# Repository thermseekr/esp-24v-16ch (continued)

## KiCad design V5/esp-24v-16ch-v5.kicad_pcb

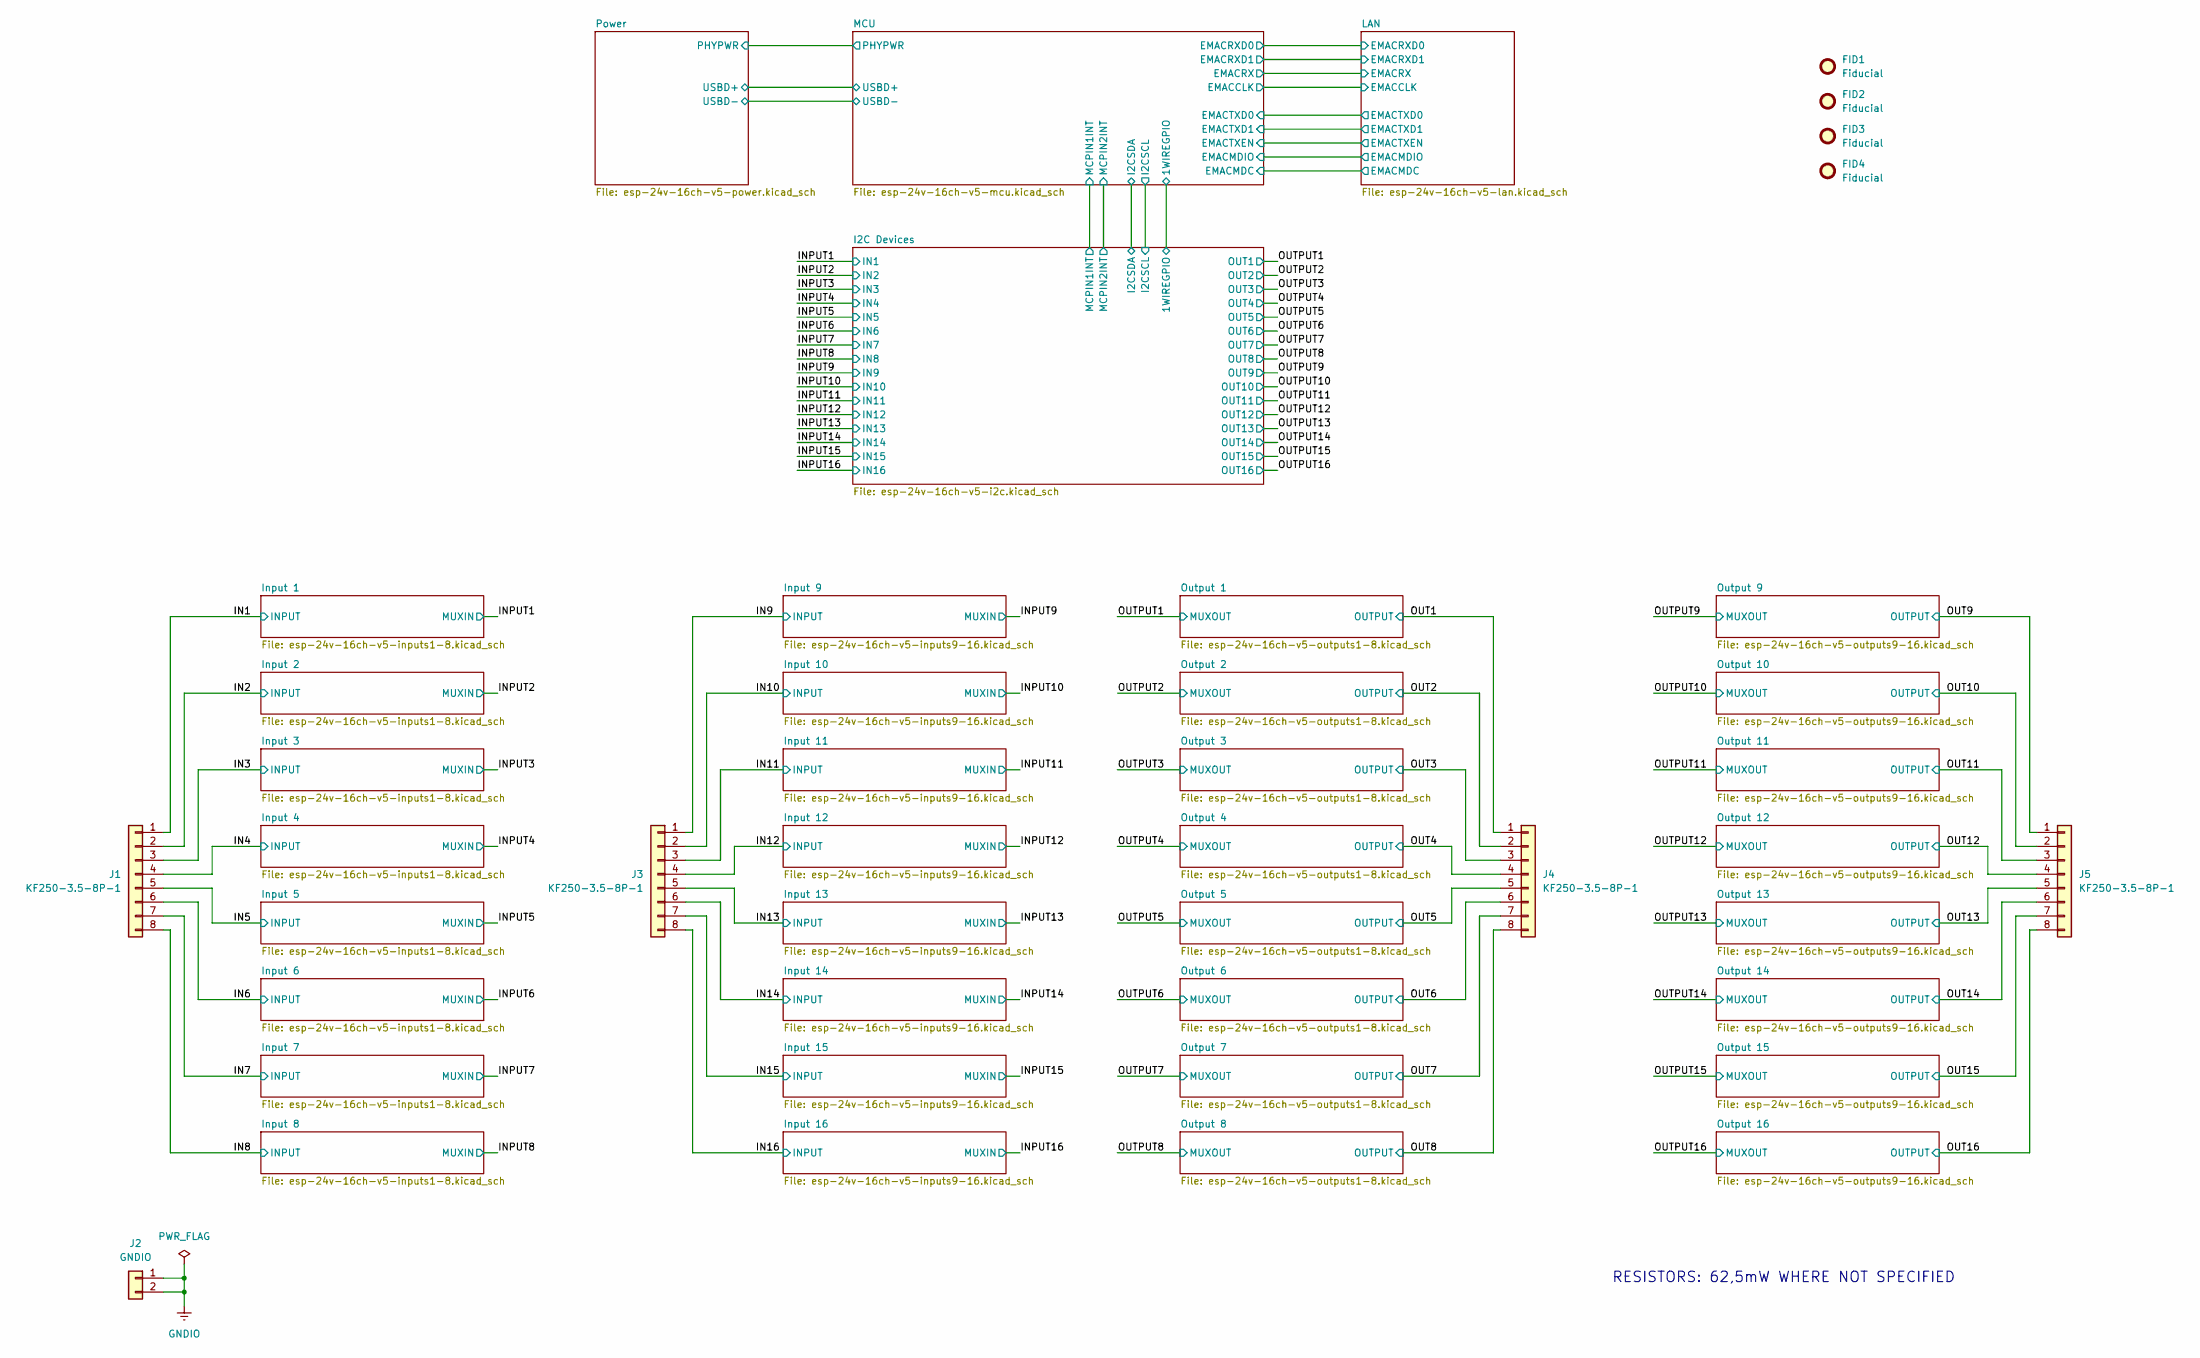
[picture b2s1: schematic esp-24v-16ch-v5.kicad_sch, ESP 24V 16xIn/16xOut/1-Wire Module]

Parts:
FID1, FID2, FID3, FID4: Fiducial; Fiducial_1mm_Mask2mm
J1, J3, J4, J5: KF250-3.5-8P-1; TerminalBlock_Wago_250-208_1x08_P3.5mm_45Degree; Mfr PN KF250-3.5-8P-1; JLCPCB BOM 1
J2: GNDIO; TerminalBlock_Wago_250-202_1x02_P3.5mm_45Degree; Mfr PN 250-202; JLCPCB BOM 1

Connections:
/IN1: J1.1; also elsewhere on the board
/IN2: J1.2; also elsewhere on the board
/IN3: J1.3; also elsewhere on the board
/IN4: J1.4; also elsewhere on the board
/IN5: J1.5; also elsewhere on the board
/IN6: J1.6; also elsewhere on the board
/IN7: J1.7; also elsewhere on the board
/IN8: J1.8; also elsewhere on the board
/IN9: J3.1; also elsewhere on the board
/IN10: J3.2; also elsewhere on the board
/IN11: J3.3; also elsewhere on the board
/IN12: J3.4; also elsewhere on the board
/IN13: J3.5; also elsewhere on the board
/IN14: J3.6; also elsewhere on the board
/IN15: J3.7; also elsewhere on the board
/IN16: J3.8; also elsewhere on the board
/OUT1: J4.1; also elsewhere on the board
/OUT2: J4.2; also elsewhere on the board
/OUT3: J4.3; also elsewhere on the board
/OUT4: J4.4; also elsewhere on the board
/OUT5: J4.5; also elsewhere on the board
/OUT6: J4.6; also elsewhere on the board
/OUT7: J4.7; also elsewhere on the board
/OUT8: J4.8; also elsewhere on the board
/OUT9: J5.1; also elsewhere on the board
/OUT10: J5.2; also elsewhere on the board
/OUT11: J5.3; also elsewhere on the board
/OUT12: J5.4; also elsewhere on the board
/OUT13: J5.5; also elsewhere on the board
/OUT14: J5.6; also elsewhere on the board
/OUT15: J5.7; also elsewhere on the board
/OUT16: J5.8; also elsewhere on the board
GNDIO: J2.1, J2.2; also elsewhere on the board

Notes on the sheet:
RESISTORS: 62,5mW WHERE NOT SPECIFIED

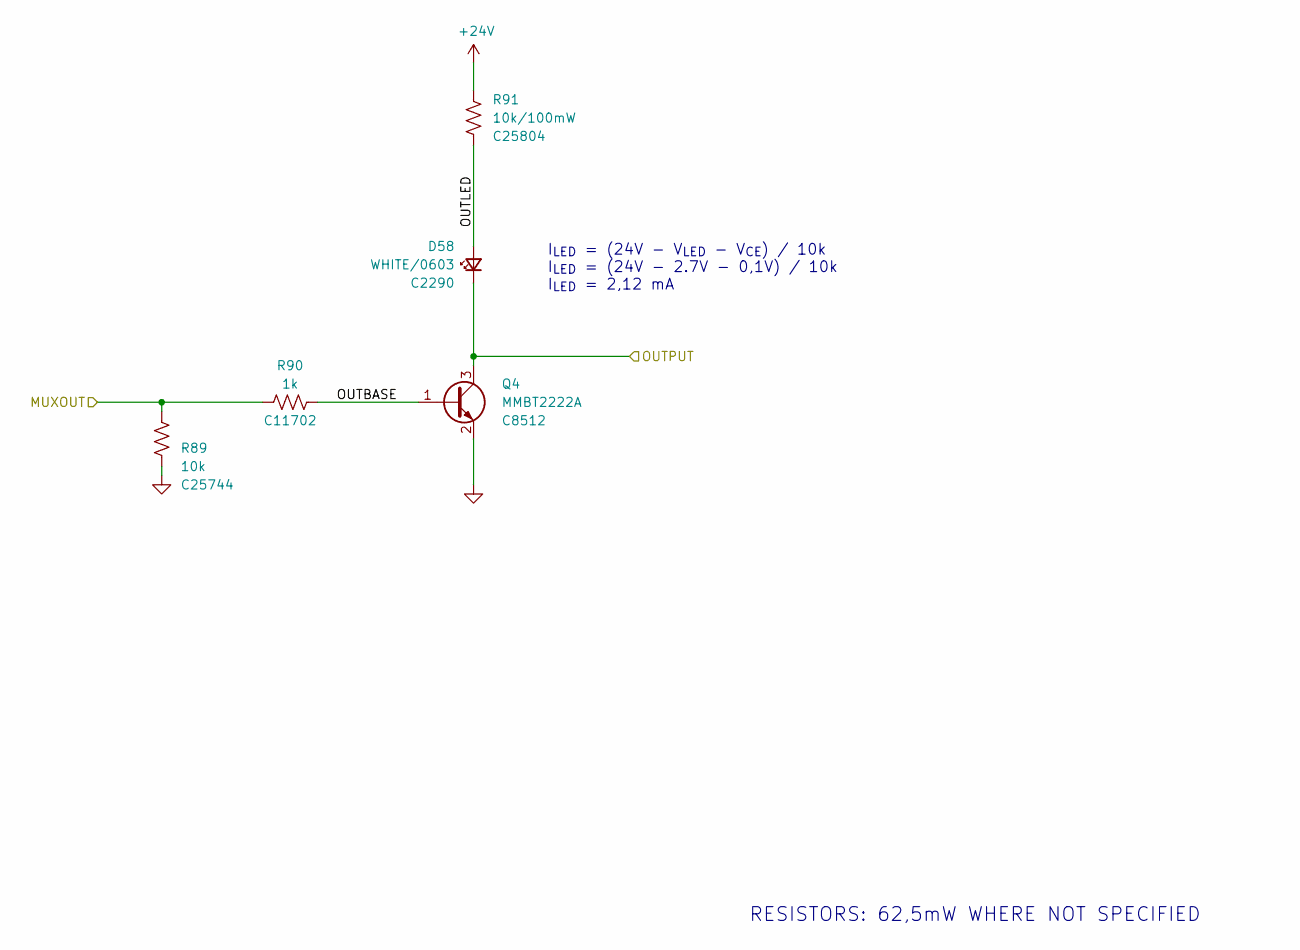
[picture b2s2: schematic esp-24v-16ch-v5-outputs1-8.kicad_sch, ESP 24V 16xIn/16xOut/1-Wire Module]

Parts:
D58: WHITE/0603; LED_0603_1608Metric; Mfr PN KT-0603W; LCSC Part # C2290
Q4: MMBT2222A; SOT-23-Narrow; Mfr PN MMBT2222A; JLCPCB BOM 1
R89: 10k; R_0402_1005Metric; Mfr PN 0402WGF1002TCE; LCSC Part # C25744
R90: 1k; R_0402_1005Metric; Mfr PN 0402WGF1001TCE; LCSC Part # C11702
R91: 10k/100mW; R_0603_1608Metric; Mfr PN 0603WAF1002T5E; LCSC Part # C25804

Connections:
+24V: R91.1; also elsewhere on the board
/OUT1: D58.1 (K), Q4.3 (C); also elsewhere on the board
/OUTPUT1: R89.2, R90.2; also elsewhere on the board
/Output 1/OUTBASE: Q4.1 (B), R90.1
/Output 1/OUTLED: D58.2 (A), R91.2
GND: Q4.2 (E), R89.1; also elsewhere on the board

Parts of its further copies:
D59, D60, D61, D62, D63, D64, D65: WHITE/0603; LED_0603_1608Metric; Mfr PN KT-0603W; LCSC Part # C2290
Q5, Q6, Q7, Q8, Q9, Q10, Q11: MMBT2222A; SOT-23-Narrow; Mfr PN MMBT2222A; JLCPCB BOM 1
R92, R95, R98, R101, R104, R107, R110: 10k; R_0402_1005Metric; Mfr PN 0402WGF1002TCE; LCSC Part # C25744
R93, R96, R99, R102, R105, R108, R111: 1k; R_0402_1005Metric; Mfr PN 0402WGF1001TCE; LCSC Part # C11702
R94, R97, R100, R103, R106, R109, R112: 10k/100mW; R_0603_1608Metric; Mfr PN 0603WAF1002T5E; LCSC Part # C25804

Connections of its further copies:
+24V: R94.1, R97.1, R100.1, R103.1, R106.1, R109.1, R112.1; also elsewhere on the board
/OUT2: D59.1 (K), Q5.3 (C); also elsewhere on the board
/OUT3: D60.1 (K), Q6.3 (C); also elsewhere on the board
/OUT4: D61.1 (K), Q7.3 (C); also elsewhere on the board
/OUT5: D62.1 (K), Q8.3 (C); also elsewhere on the board
/OUT6: D63.1 (K), Q9.3 (C); also elsewhere on the board
/OUT7: D64.1 (K), Q10.3 (C); also elsewhere on the board
/OUT8: D65.1 (K), Q11.3 (C); also elsewhere on the board
/OUTPUT2: R92.2, R93.2; also elsewhere on the board
/OUTPUT3: R95.2, R96.2; also elsewhere on the board
/OUTPUT4: R98.2, R99.2; also elsewhere on the board
/OUTPUT5: R101.2, R102.2; also elsewhere on the board
/OUTPUT6: R104.2, R105.2; also elsewhere on the board
/OUTPUT7: R107.2, R108.2; also elsewhere on the board
/OUTPUT8: R110.2, R111.2; also elsewhere on the board
/Output 2/OUTBASE: Q5.1 (B), R93.1
/Output 2/OUTLED: D59.2 (A), R94.2
/Output 3/OUTBASE: Q6.1 (B), R96.1
/Output 3/OUTLED: D60.2 (A), R97.2
/Output 4/OUTBASE: Q7.1 (B), R99.1
/Output 4/OUTLED: D61.2 (A), R100.2
/Output 5/OUTBASE: Q8.1 (B), R102.1
/Output 5/OUTLED: D62.2 (A), R103.2
/Output 6/OUTBASE: Q9.1 (B), R105.1
/Output 6/OUTLED: D63.2 (A), R106.2
/Output 7/OUTBASE: Q10.1 (B), R108.1
/Output 7/OUTLED: D64.2 (A), R109.2
/Output 8/OUTBASE: Q11.1 (B), R111.1
/Output 8/OUTLED: D65.2 (A), R112.2
GND: Q5.2 (E), Q6.2 (E), Q7.2 (E), Q8.2 (E), Q9.2 (E), Q10.2 (E), Q11.2 (E), R92.1, R95.1, R98.1, R101.1, R104.1, R107.1, R110.1; also elsewhere on the board

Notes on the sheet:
I_{LED} = (24V - V_{LED} - V_{CE}) / 10k I_{LED} = (24V - 2.7V - 0,1V) / 10k I_{LED} = 2,12 mA
RESISTORS: 62,5mW WHERE NOT SPECIFIED

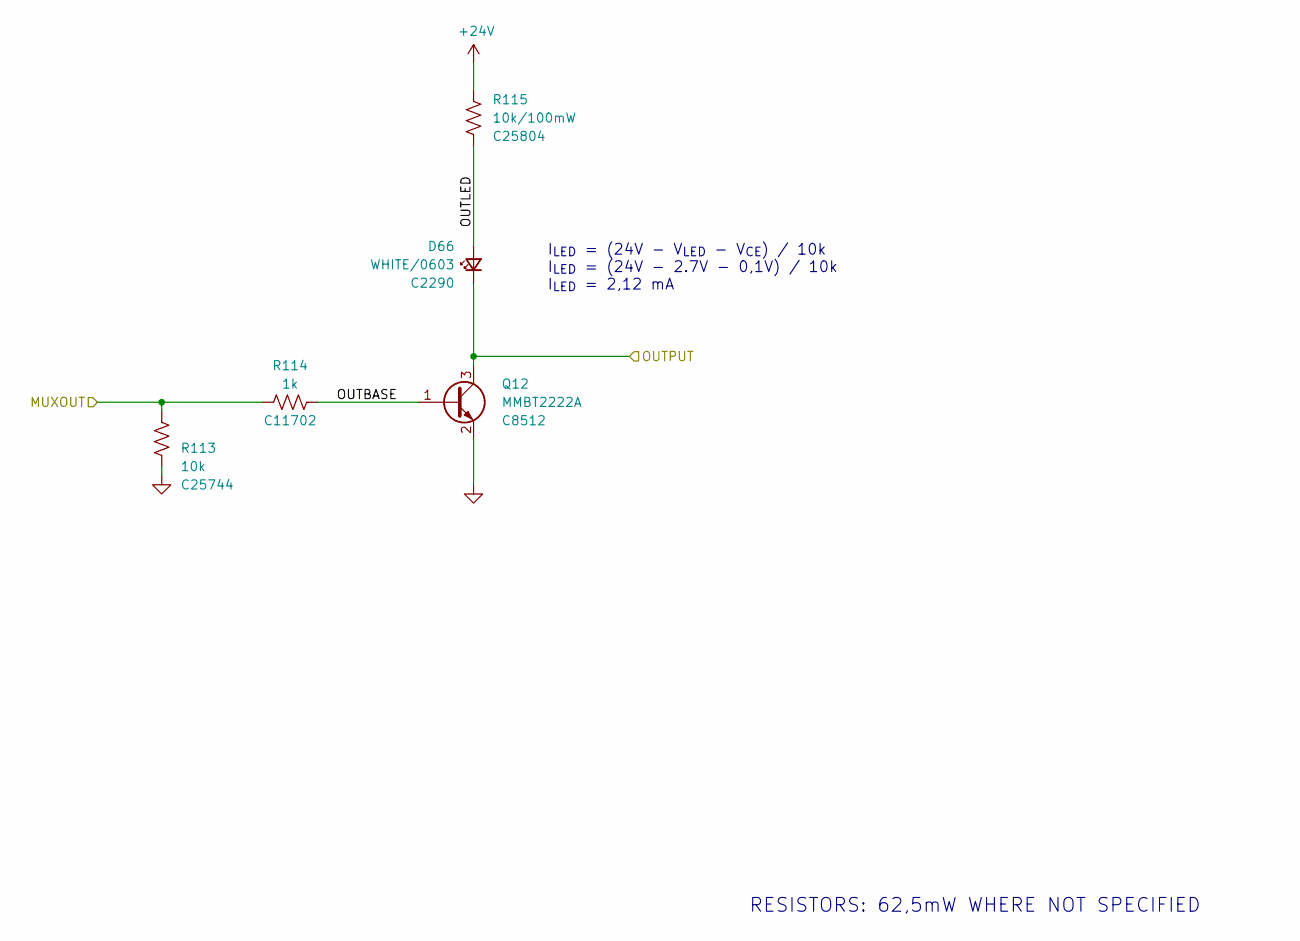
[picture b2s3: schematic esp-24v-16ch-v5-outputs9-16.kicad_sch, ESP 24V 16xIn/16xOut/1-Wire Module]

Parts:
D66: WHITE/0603; LED_0603_1608Metric; Mfr PN KT-0603W; LCSC Part # C2290
Q12: MMBT2222A; SOT-23-Narrow; Mfr PN MMBT2222A; JLCPCB BOM 1
R113: 10k; R_0402_1005Metric; Mfr PN 0402WGF1002TCE; LCSC Part # C25744
R114: 1k; R_0402_1005Metric; Mfr PN 0402WGF1001TCE; LCSC Part # C11702
R115: 10k/100mW; R_0603_1608Metric; Mfr PN 0603WAF1002T5E; LCSC Part # C25804

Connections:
+24V: R115.1; also elsewhere on the board
/OUT9: D66.1 (K), Q12.3 (C); also elsewhere on the board
/OUTPUT9: R113.2, R114.2; also elsewhere on the board
/Output 9/OUTBASE: Q12.1 (B), R114.1
/Output 9/OUTLED: D66.2 (A), R115.2
GND: Q12.2 (E), R113.1; also elsewhere on the board

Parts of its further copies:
D67, D68, D69, D70, D71, D72, D73: WHITE/0603; LED_0603_1608Metric; Mfr PN KT-0603W; LCSC Part # C2290
Q13, Q14, Q15, Q16, Q17, Q18, Q19: MMBT2222A; SOT-23-Narrow; Mfr PN MMBT2222A; JLCPCB BOM 1
R116, R119, R122, R125, R128, R131, R134: 10k; R_0402_1005Metric; Mfr PN 0402WGF1002TCE; LCSC Part # C25744
R117, R120, R123, R126, R129, R132, R135: 1k; R_0402_1005Metric; Mfr PN 0402WGF1001TCE; LCSC Part # C11702
R118, R121, R124, R127, R130, R133, R136: 10k/100mW; R_0603_1608Metric; Mfr PN 0603WAF1002T5E; LCSC Part # C25804

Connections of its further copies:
+24V: R118.1, R121.1, R124.1, R127.1, R130.1, R133.1, R136.1; also elsewhere on the board
/OUT10: D67.1 (K), Q13.3 (C); also elsewhere on the board
/OUT11: D68.1 (K), Q14.3 (C); also elsewhere on the board
/OUT12: D69.1 (K), Q15.3 (C); also elsewhere on the board
/OUT13: D70.1 (K), Q16.3 (C); also elsewhere on the board
/OUT14: D71.1 (K), Q17.3 (C); also elsewhere on the board
/OUT15: D72.1 (K), Q18.3 (C); also elsewhere on the board
/OUT16: D73.1 (K), Q19.3 (C); also elsewhere on the board
/OUTPUT10: R116.2, R117.2; also elsewhere on the board
/OUTPUT11: R119.2, R120.2; also elsewhere on the board
/OUTPUT12: R122.2, R123.2; also elsewhere on the board
/OUTPUT13: R125.2, R126.2; also elsewhere on the board
/OUTPUT14: R128.2, R129.2; also elsewhere on the board
/OUTPUT15: R131.2, R132.2; also elsewhere on the board
/OUTPUT16: R134.2, R135.2; also elsewhere on the board
/Output 10/OUTBASE: Q13.1 (B), R117.1
/Output 10/OUTLED: D67.2 (A), R118.2
/Output 11/OUTBASE: Q14.1 (B), R120.1
/Output 11/OUTLED: D68.2 (A), R121.2
/Output 12/OUTBASE: Q15.1 (B), R123.1
/Output 12/OUTLED: D69.2 (A), R124.2
/Output 13/OUTBASE: Q16.1 (B), R126.1
/Output 13/OUTLED: D70.2 (A), R127.2
/Output 14/OUTBASE: Q17.1 (B), R129.1
/Output 14/OUTLED: D71.2 (A), R130.2
/Output 15/OUTBASE: Q18.1 (B), R132.1
/Output 15/OUTLED: D72.2 (A), R133.2
/Output 16/OUTBASE: Q19.1 (B), R135.1
/Output 16/OUTLED: D73.2 (A), R136.2
GND: Q13.2 (E), Q14.2 (E), Q15.2 (E), Q16.2 (E), Q17.2 (E), Q18.2 (E), Q19.2 (E), R116.1, R119.1, R122.1, R125.1, R128.1, R131.1, R134.1; also elsewhere on the board

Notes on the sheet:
RESISTORS: 62,5mW WHERE NOT SPECIFIED
I_{LED} = (24V - V_{LED} - V_{CE}) / 10k I_{LED} = (24V - 2.7V - 0,1V) / 10k I_{LED} = 2,12 mA

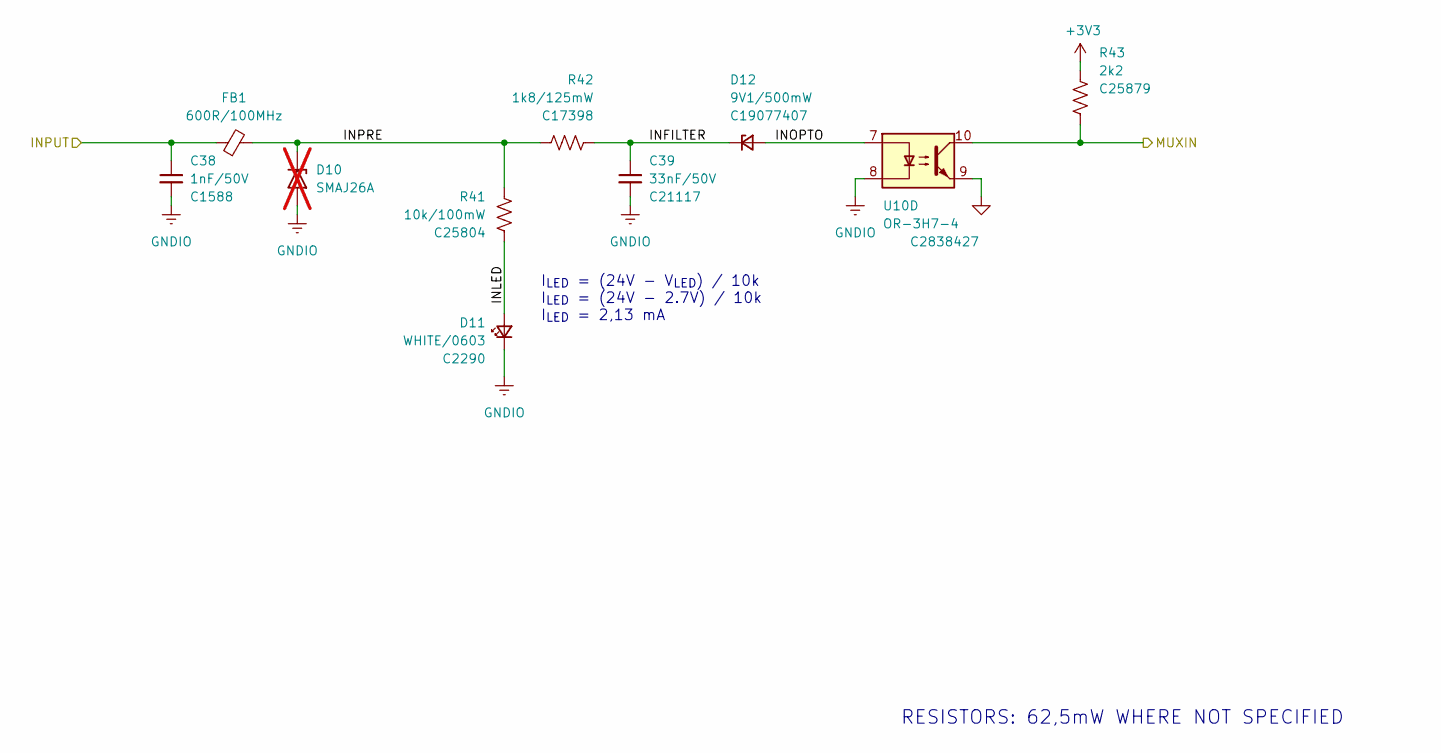
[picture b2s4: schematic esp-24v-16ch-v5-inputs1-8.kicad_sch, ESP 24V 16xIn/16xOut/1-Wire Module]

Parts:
C38: 1nF/50V; C_0603_1608Metric; Mfr PN CL10B102KB8NNNC; LCSC Part # C1588
C39: 33nF/50V; C_0603_1608Metric; Mfr PN CL10B333KB8NNNC; LCSC Part # C21117
D10: SMAJ26A; D_SMA; Mfr PN SMAJ26A; JLCPCB BOM 1; not fitted
D11: WHITE/0603; LED_0603_1608Metric; Mfr PN KT-0603W; LCSC Part # C2290
D12: 9V1/500mW; D_SOD-123; Mfr PN BZT52C9V1; JLCPCB BOM 1
FB1: 600R/100MHz; R_0603_1608Metric; Mfr PN BLM18KG601SN1D; JLCPCB BOM 1
R41: 10k/100mW; R_0603_1608Metric; Mfr PN 0603WAF1002T5E; LCSC Part # C25804
R42: 1k8/125mW; R_0805_2012Metric; Mfr PN 0805W8F1801T5E; LCSC Part # C17398
R43: 2k2; R_0402_1005Metric; Mfr PN 0402WGF2201TCE; LCSC Part # C25879
U10: OR-3H7-4; SOP-16_4.4x10.4mm_P1.27mm; Mfr PN OR-3H7-4GB-TA1-G; JLCPCB BOM 1

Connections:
+3V3: R43.1; also elsewhere on the board
/IN1: C38.1, FB1.1; also elsewhere on the board
/INPUT1: R43.2, U10.10; also elsewhere on the board
/INPUT2: U10.12; also elsewhere on the board
/INPUT3: U10.14; also elsewhere on the board
/INPUT4: U10.16; also elsewhere on the board
/Input 1/INFILTER: C39.1, D12.1 (K), R42.1
/Input 1/INLED: D11.2 (A), R41.2
/Input 1/INOPTO: D12.2 (A), U10.7
/Input 1/INPRE: FB1.2, R41.1, R42.2
/Input 2/INOPTO: U10.5; also elsewhere on the board
/Input 3/INOPTO: U10.3; also elsewhere on the board
/Input 4/INOPTO: U10.1; also elsewhere on the board
GND: U10.9, U10.11, U10.13, U10.15; also elsewhere on the board
GNDIO: C38.2, C39.2, D10.2 (A2), D11.1 (K), U10.2, U10.4, U10.6, U10.8; also elsewhere on the board

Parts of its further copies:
C40, C42, C44, C46, C48, C50, C52: 1nF/50V; C_0603_1608Metric; Mfr PN CL10B102KB8NNNC; LCSC Part # C1588
C41, C43, C45, C47, C49, C51, C53: 33nF/50V; C_0603_1608Metric; Mfr PN CL10B333KB8NNNC; LCSC Part # C21117
D14, D17, D20, D23, D26, D29, D32: WHITE/0603; LED_0603_1608Metric; Mfr PN KT-0603W; LCSC Part # C2290
D15, D18, D21, D24, D27, D30, D33: 9V1/500mW; D_SOD-123; Mfr PN BZT52C9V1; JLCPCB BOM 1
FB2, FB3, FB4, FB5, FB6, FB7, FB8: 600R/100MHz; R_0603_1608Metric; Mfr PN BLM18KG601SN1D; JLCPCB BOM 1
R44, R47, R50, R53, R56, R59, R62: 10k/100mW; R_0603_1608Metric; Mfr PN 0603WAF1002T5E; LCSC Part # C25804
R45, R48, R51, R54, R57, R60, R63: 1k8/125mW; R_0805_2012Metric; Mfr PN 0805W8F1801T5E; LCSC Part # C17398
R46, R49, R52, R55, R58, R61, R64: 2k2; R_0402_1005Metric; Mfr PN 0402WGF2201TCE; LCSC Part # C25879
U11: OR-3H7-4; SOP-16_4.4x10.4mm_P1.27mm; Mfr PN OR-3H7-4GB-TA1-G; JLCPCB BOM 1

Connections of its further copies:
+3V3: R46.1, R49.1, R52.1, R55.1, R58.1, R61.1, R64.1; also elsewhere on the board
/IN2: C40.1, FB2.1; also elsewhere on the board
/IN3: C42.1, FB3.1; also elsewhere on the board
/IN4: C44.1, FB4.1; also elsewhere on the board
/IN5: C46.1, FB5.1; also elsewhere on the board
/IN6: C48.1, FB6.1; also elsewhere on the board
/IN7: C50.1, FB7.1; also elsewhere on the board
/IN8: C52.1, FB8.1; also elsewhere on the board
/INPUT2: R46.2; also elsewhere on the board
/INPUT3: R49.2; also elsewhere on the board
/INPUT4: R52.2; also elsewhere on the board
/INPUT5: R55.2, U11.10; also elsewhere on the board
/INPUT6: R58.2, U11.12; also elsewhere on the board
/INPUT7: R61.2, U11.14; also elsewhere on the board
/INPUT8: R64.2, U11.16; also elsewhere on the board
/Input 2/INFILTER: C41.1, D15.1 (K), R45.1
/Input 2/INLED: D14.2 (A), R44.2
/Input 2/INOPTO: D15.2 (A); also elsewhere on the board
/Input 2/INPRE: FB2.2, R44.1, R45.2
/Input 3/INFILTER: C43.1, D18.1 (K), R48.1
/Input 3/INLED: D17.2 (A), R47.2
/Input 3/INOPTO: D18.2 (A); also elsewhere on the board
/Input 3/INPRE: FB3.2, R47.1, R48.2
/Input 4/INFILTER: C45.1, D21.1 (K), R51.1
/Input 4/INLED: D20.2 (A), R50.2
/Input 4/INOPTO: D21.2 (A); also elsewhere on the board
/Input 4/INPRE: FB4.2, R50.1, R51.2
/Input 5/INFILTER: C47.1, D24.1 (K), R54.1
/Input 5/INLED: D23.2 (A), R53.2
/Input 5/INOPTO: D24.2 (A), U11.7
/Input 5/INPRE: FB5.2, R53.1, R54.2
/Input 6/INFILTER: C49.1, D27.1 (K), R57.1
/Input 6/INLED: D26.2 (A), R56.2
/Input 6/INOPTO: D27.2 (A), U11.5
/Input 6/INPRE: FB6.2, R56.1, R57.2
/Input 7/INFILTER: C51.1, D30.1 (K), R60.1
/Input 7/INLED: D29.2 (A), R59.2
/Input 7/INOPTO: D30.2 (A), U11.3
/Input 7/INPRE: FB7.2, R59.1, R60.2
/Input 8/INFILTER: C53.1, D33.1 (K), R63.1
/Input 8/INLED: D32.2 (A), R62.2
/Input 8/INOPTO: D33.2 (A), U11.1
/Input 8/INPRE: FB8.2, R62.1, R63.2
GND: U11.9, U11.11, U11.13, U11.15; also elsewhere on the board
GNDIO: C40.2, C41.2, C42.2, C43.2, C44.2, C45.2, C46.2, C47.2, C48.2, C49.2, C50.2, C51.2, C52.2, C53.2, D14.1 (K), D17.1 (K), D20.1 (K), D23.1 (K), D26.1 (K), D29.1 (K), D32.1 (K), U11.2, U11.4, U11.6, U11.8; also elsewhere on the board

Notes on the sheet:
I_{LED} = (24V - V_{LED}) / 10k I_{LED} = (24V - 2.7V) / 10k I_{LED} = 2,13 mA
RESISTORS: 62,5mW WHERE NOT SPECIFIED

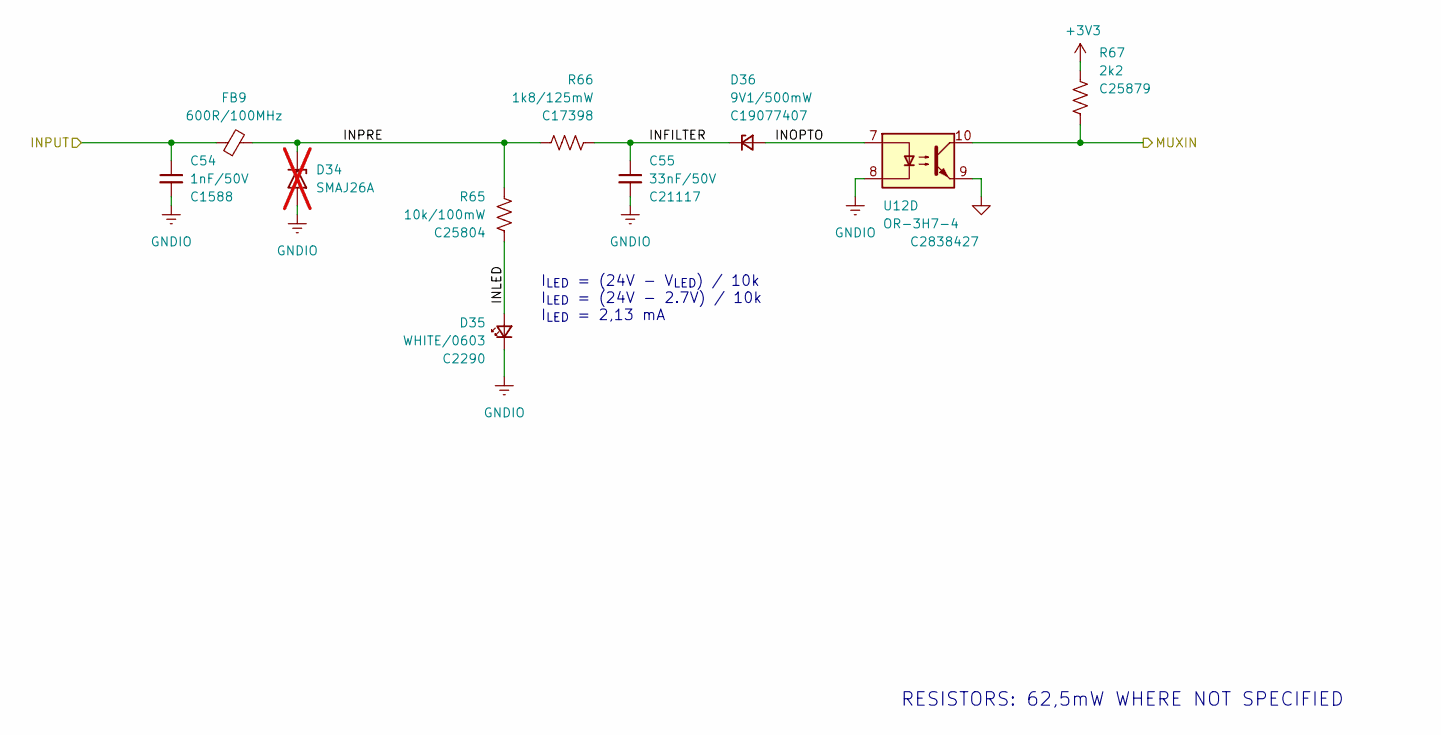
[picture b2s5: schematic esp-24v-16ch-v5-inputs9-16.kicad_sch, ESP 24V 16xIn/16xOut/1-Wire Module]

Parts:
C54: 1nF/50V; C_0603_1608Metric; Mfr PN CL10B102KB8NNNC; LCSC Part # C1588
C55: 33nF/50V; C_0603_1608Metric; Mfr PN CL10B333KB8NNNC; LCSC Part # C21117
D34: SMAJ26A; D_SMA; Mfr PN SMAJ26A; JLCPCB BOM 1; not fitted
D35: WHITE/0603; LED_0603_1608Metric; Mfr PN KT-0603W; LCSC Part # C2290
D36: 9V1/500mW; D_SOD-123; Mfr PN BZT52C9V1; JLCPCB BOM 1
FB9: 600R/100MHz; R_0603_1608Metric; Mfr PN BLM18KG601SN1D; JLCPCB BOM 1
R65: 10k/100mW; R_0603_1608Metric; Mfr PN 0603WAF1002T5E; LCSC Part # C25804
R66: 1k8/125mW; R_0805_2012Metric; Mfr PN 0805W8F1801T5E; LCSC Part # C17398
R67: 2k2; R_0402_1005Metric; Mfr PN 0402WGF2201TCE; LCSC Part # C25879
U12: OR-3H7-4; SOP-16_4.4x10.4mm_P1.27mm; Mfr PN OR-3H7-4GB-TA1-G; JLCPCB BOM 1

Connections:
+3V3: R67.1; also elsewhere on the board
/IN9: C54.1, FB9.1; also elsewhere on the board
/INPUT9: R67.2, U12.10; also elsewhere on the board
/INPUT10: U12.12; also elsewhere on the board
/INPUT11: U12.14; also elsewhere on the board
/INPUT12: U12.16; also elsewhere on the board
/Input 9/INFILTER: C55.1, D36.1 (K), R66.1
/Input 9/INLED: D35.2 (A), R65.2
/Input 9/INOPTO: D36.2 (A), U12.7
/Input 9/INPRE: FB9.2, R65.1, R66.2
/Input 10/INOPTO: U12.5; also elsewhere on the board
/Input 11/INOPTO: U12.3; also elsewhere on the board
/Input 12/INOPTO: U12.1; also elsewhere on the board
GND: U12.9, U12.11, U12.13, U12.15; also elsewhere on the board
GNDIO: C54.2, C55.2, D34.2 (A2), D35.1 (K), U12.2, U12.4, U12.6, U12.8; also elsewhere on the board

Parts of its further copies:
C56, C58, C60, C62, C64, C66, C68: 1nF/50V; C_0603_1608Metric; Mfr PN CL10B102KB8NNNC; LCSC Part # C1588
C57, C59, C61, C63, C65, C67, C69: 33nF/50V; C_0603_1608Metric; Mfr PN CL10B333KB8NNNC; LCSC Part # C21117
D38, D41, D44, D47, D50, D53, D56: WHITE/0603; LED_0603_1608Metric; Mfr PN KT-0603W; LCSC Part # C2290
D39, D42, D45, D48, D51, D54, D57: 9V1/500mW; D_SOD-123; Mfr PN BZT52C9V1; JLCPCB BOM 1
FB10, FB11, FB12, FB13, FB14, FB15, FB16: 600R/100MHz; R_0603_1608Metric; Mfr PN BLM18KG601SN1D; JLCPCB BOM 1
R68, R71, R74, R77, R80, R83, R86: 10k/100mW; R_0603_1608Metric; Mfr PN 0603WAF1002T5E; LCSC Part # C25804
R69, R72, R75, R78, R81, R84, R87: 1k8/125mW; R_0805_2012Metric; Mfr PN 0805W8F1801T5E; LCSC Part # C17398
R70, R73, R76, R79, R82, R85, R88: 2k2; R_0402_1005Metric; Mfr PN 0402WGF2201TCE; LCSC Part # C25879
U13: OR-3H7-4; SOP-16_4.4x10.4mm_P1.27mm; Mfr PN OR-3H7-4GB-TA1-G; JLCPCB BOM 1

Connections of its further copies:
+3V3: R70.1, R73.1, R76.1, R79.1, R82.1, R85.1, R88.1; also elsewhere on the board
/IN10: C56.1, FB10.1; also elsewhere on the board
/IN11: C58.1, FB11.1; also elsewhere on the board
/IN12: C60.1, FB12.1; also elsewhere on the board
/IN13: C62.1, FB13.1; also elsewhere on the board
/IN14: C64.1, FB14.1; also elsewhere on the board
/IN15: C66.1, FB15.1; also elsewhere on the board
/IN16: C68.1, FB16.1; also elsewhere on the board
/INPUT10: R70.2; also elsewhere on the board
/INPUT11: R73.2; also elsewhere on the board
/INPUT12: R76.2; also elsewhere on the board
/INPUT13: R79.2, U13.10; also elsewhere on the board
/INPUT14: R82.2, U13.12; also elsewhere on the board
/INPUT15: R85.2, U13.14; also elsewhere on the board
/INPUT16: R88.2, U13.16; also elsewhere on the board
/Input 10/INFILTER: C57.1, D39.1 (K), R69.1
/Input 10/INLED: D38.2 (A), R68.2
/Input 10/INOPTO: D39.2 (A); also elsewhere on the board
/Input 10/INPRE: FB10.2, R68.1, R69.2
/Input 11/INFILTER: C59.1, D42.1 (K), R72.1
/Input 11/INLED: D41.2 (A), R71.2
/Input 11/INOPTO: D42.2 (A); also elsewhere on the board
/Input 11/INPRE: FB11.2, R71.1, R72.2
/Input 12/INFILTER: C61.1, D45.1 (K), R75.1
/Input 12/INLED: D44.2 (A), R74.2
/Input 12/INOPTO: D45.2 (A); also elsewhere on the board
/Input 12/INPRE: FB12.2, R74.1, R75.2
/Input 13/INFILTER: C63.1, D48.1 (K), R78.1
/Input 13/INLED: D47.2 (A), R77.2
/Input 13/INOPTO: D48.2 (A), U13.7
/Input 13/INPRE: FB13.2, R77.1, R78.2
/Input 14/INFILTER: C65.1, D51.1 (K), R81.1
/Input 14/INLED: D50.2 (A), R80.2
/Input 14/INOPTO: D51.2 (A), U13.5
/Input 14/INPRE: FB14.2, R80.1, R81.2
/Input 15/INFILTER: C67.1, D54.1 (K), R84.1
/Input 15/INLED: D53.2 (A), R83.2
/Input 15/INOPTO: D54.2 (A), U13.3
/Input 15/INPRE: FB15.2, R83.1, R84.2
/Input 16/INFILTER: C69.1, D57.1 (K), R87.1
/Input 16/INLED: D56.2 (A), R86.2
/Input 16/INOPTO: D57.2 (A), U13.1
/Input 16/INPRE: FB16.2, R86.1, R87.2
GND: U13.9, U13.11, U13.13, U13.15; also elsewhere on the board
GNDIO: C56.2, C57.2, C58.2, C59.2, C60.2, C61.2, C62.2, C63.2, C64.2, C65.2, C66.2, C67.2, C68.2, C69.2, D38.1 (K), D41.1 (K), D44.1 (K), D47.1 (K), D50.1 (K), D53.1 (K), D56.1 (K), U13.2, U13.4, U13.6, U13.8; also elsewhere on the board

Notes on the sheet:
I_{LED} = (24V - V_{LED}) / 10k I_{LED} = (24V - 2.7V) / 10k I_{LED} = 2,13 mA
RESISTORS: 62,5mW WHERE NOT SPECIFIED

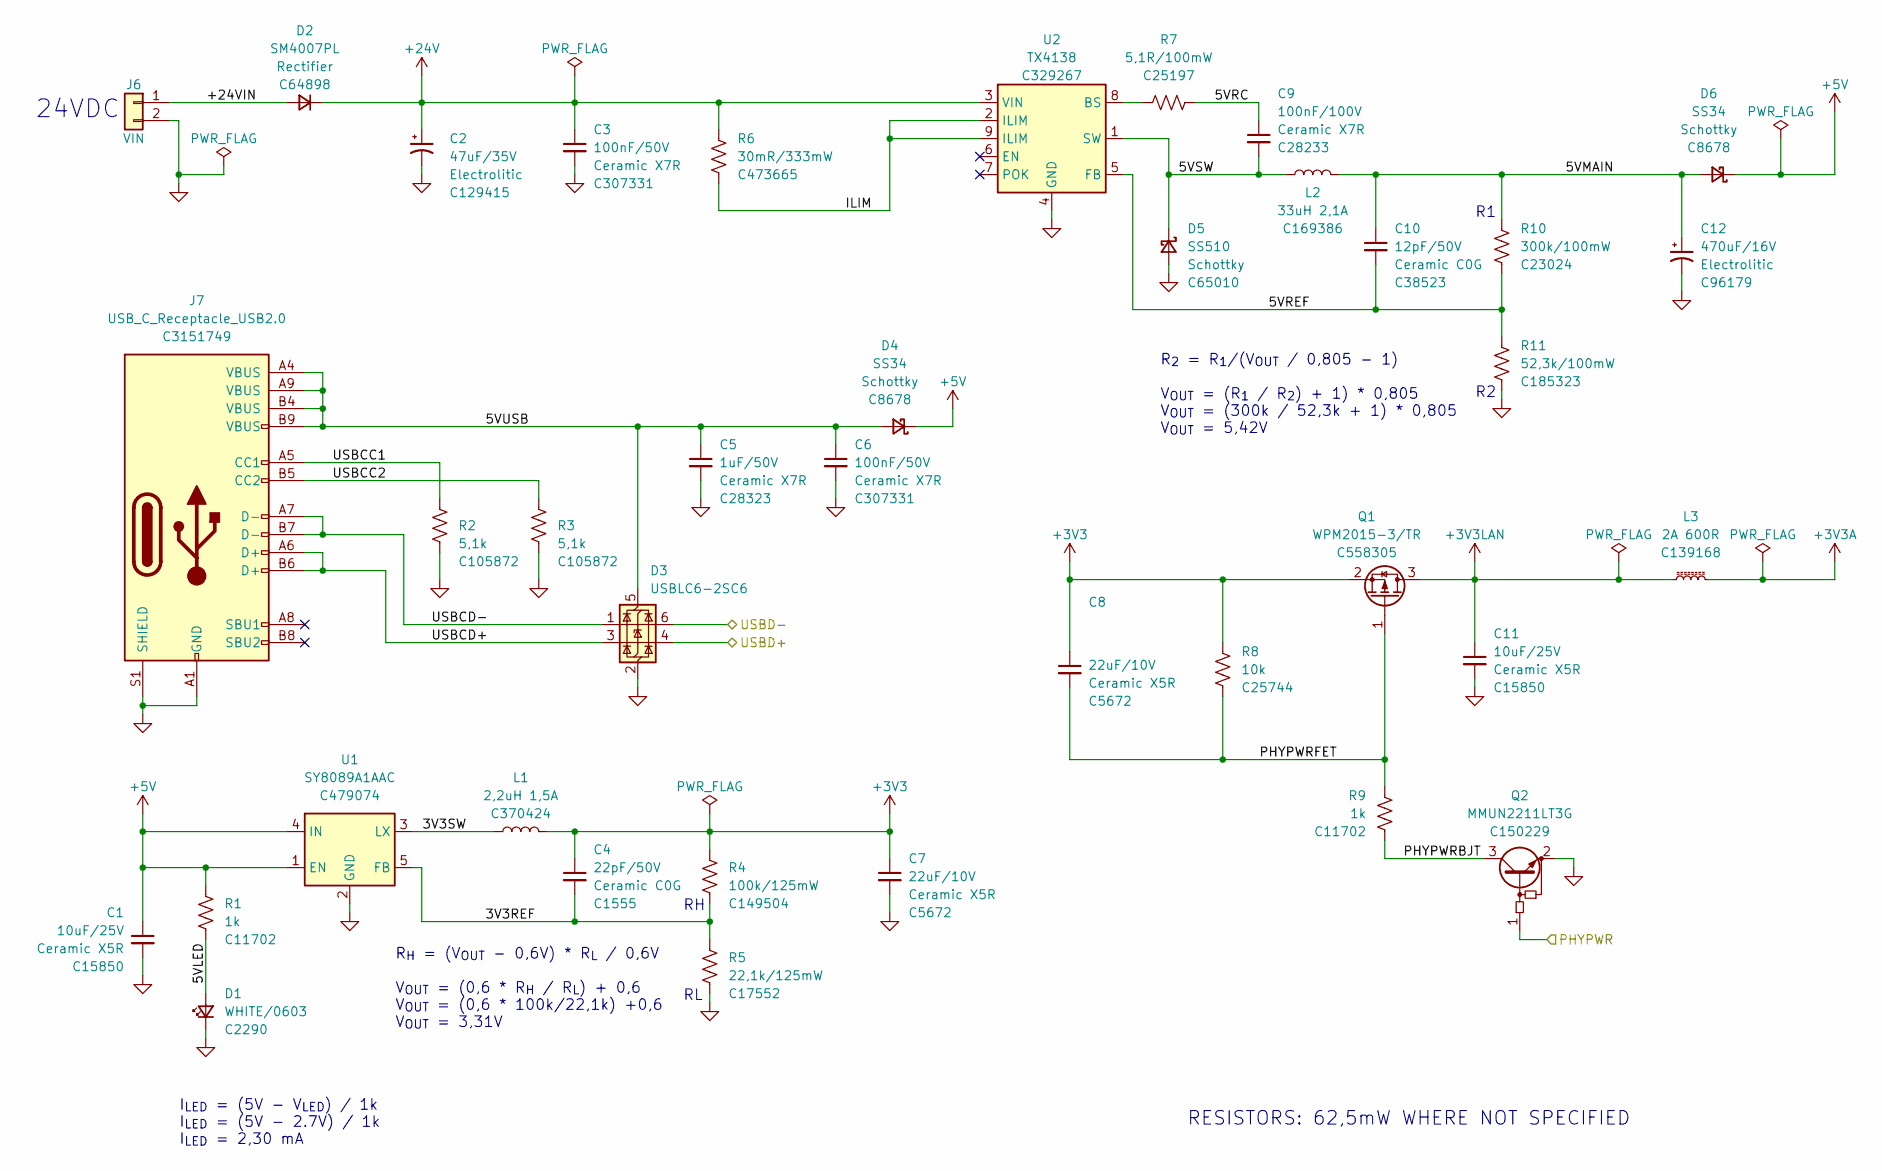
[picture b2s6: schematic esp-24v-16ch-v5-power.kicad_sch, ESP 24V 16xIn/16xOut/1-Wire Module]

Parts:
C1, C11: 10uF/25V; C_0805_2012Metric; Mfr PN CL21A106KAYNNNE; JLCPCB BOM 1
C2: 47uF/35V; CP_Elec_6.3x5.4; Mfr PN CK1V470M-CRE54; JLCPCB BOM 1
C3, C6: 100nF/50V; C_0402_1005Metric; Mfr PN CL05B104KB54PNC; JLCPCB BOM 1
C4: 22pF/50V; C_0402_1005Metric; Mfr PN 0402CG220J500NT; JLCPCB BOM 1
C5: 1uF/50V; C_0805_2012Metric; Mfr PN CL21B105KBFNNNE; JLCPCB BOM 1
C7, C8: 22uF/10V; C_1206_3216Metric; Mfr PN CL31A226KPHNNNE; JLCPCB BOM 1
C9: 100nF/100V; C_0805_2012Metric; Mfr PN CL21B104KCFNNNE; LCSC Part # C28233
C10: 12pF/50V; C_0603_1608Metric; Mfr PN CL10C120JB8NNNC; JLCPCB BOM 1
C12: 470uF/16V; CP_Elec_8x10.5; Mfr PN CS1C471M-CRF10; JLCPCB BOM 1
D1: WHITE/0603; LED_0603_1608Metric; Mfr PN KT-0603W; LCSC Part # C2290
D2: SM4007PL; D_SOD-123; Mfr PN SM4007PL; LCSC Part # C64898
D3: USBLC6-2SC6; SOT-23-6; Mfr PN USBLC6-2SC6; JLCPCB BOM 1
D4, D6: SS34; D_SMA; Mfr PN SS34; JLCPCB BOM 1
D5: SS510; D_SMA; Mfr PN SS510; JLCPCB BOM 1
J6: VIN; TerminalBlock_Wago_250-202_1x02_P3.5mm_45Degree; Mfr PN 250-202; JLCPCB BOM 1
J7: USB_C_Receptacle_USB2.0; USB_C_Receptacle_ShouHan_TYPE-C-16PLT-H10.0; Mfr PN TYPE-C 16PLT-H10.0; JLCPCB BOM 1
L1: 2,2uH 1,5A; L_3x3mm_h1.5mm; Mfr PN SPH3015H2R2MT; JLCPCB BOM 1
L2: 33uH 2,1A; L_12x12mm_h6mm; Mfr PN SWRB1205S-330MT; JLCPCB BOM 1
L3: 2A 600R; L_0805_2012Metric; Mfr PN CBM201209U601T; JLCPCB BOM 1
Q1: WPM2015-3/TR; SOT-23; Mfr PN WPM2015-3/TR; JLCPCB BOM 1
Q2: MMUN2211LT3G; SOT-23; Mfr PN MMUN2211LT3G; LCSC Part # C150229
R1, R9: 1k; R_0402_1005Metric; Mfr PN 0402WGF1001TCE; LCSC Part # C11702
R2, R3: 5,1k; R_0402_1005Metric; Mfr PN RC0402FR-075K1L; JLCPCB BOM 1
R4: 100k/125mW; R_0805_2012Metric; Mfr PN 0805W8F1003T5E; JLCPCB BOM 1
R5: 22,1k/125mW; R_0805_2012Metric; Mfr PN 0805W8F2212T5E; JLCPCB BOM 1
R6: 30mR/333mW; R_1206_3216Metric; Mfr PN 1206W3F300MT5E; LCSC Part # C473665
R7: 5,1R/100mW; R_0603_1608Metric; Mfr PN 0603WAF510KT5E; LCSC Part # C25197
R8: 10k; R_0402_1005Metric; Mfr PN 0402WGF1002TCE; LCSC Part # C25744
R10: 300k/100mW; R_0603_1608Metric; Mfr PN 0603WAF3003T5E; JLCPCB BOM 1
R11: 52,3k/100mW; R_0603_1608Metric; Mfr PN RC0603FR-0752K3L; JLCPCB BOM 1
U1: SY8089A1AAC; SOT-23-5_Shorter_Pins; Mfr PN SY8089A1AAC; JLCPCB BOM 1
U2: TX4138; SOIC-8-1EP_3.9x4.9mm_P1.27mm_EP2.41x3.81mm_ThermalVias; Mfr PN TX4138; JLCPCB BOM 1

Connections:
+3V3: C4.1, C7.1, C8.1, L1.2, Q1.2 (S), R4.1, R8.1; also elsewhere on the board
+3V3A: L3.2; also elsewhere on the board
+3V3LAN: C11.1, L3.1, Q1.3 (D); also elsewhere on the board
+5V: C1.1, D4.1 (K), D6.1 (K), R1.1, U1.1 (EN), U1.4 (IN); also elsewhere on the board
+24V: C2.1, C3.1, D2.1 (K), R6.1, U2.3 (VIN); also elsewhere on the board
/MCU/PHYPWR: Q2.1 (B); also elsewhere on the board
/MCU/USBD+: D3.4 (I/O2); also elsewhere on the board
/MCU/USBD-: D3.6 (I/O1); also elsewhere on the board
/Power/3V3REF: C4.2, R4.2, R5.1, U1.5 (FB)
/Power/3V3SW: L1.1, U1.3 (LX)
/Power/5VLED: D1.2 (A), R1.2
/Power/5VMAIN: C10.1, C12.1, D6.2 (A), L2.2, R10.1
/Power/5VRC: C9.1, R7.1
/Power/5VREF: C10.2, R10.2, R11.1, U2.5 (FB)
/Power/5VSW: C9.2, D5.1 (K), L2.1, U2.1 (SW)
/Power/5VUSB: C5.1, C6.1, D3.5 (VBUS), D4.2 (A), J7.A4 (VBUS), J7.A9 (VBUS), J7.B4 (VBUS), J7.B9 (VBUS)
/Power/+24VIN: D2.2 (A), J6.1
/Power/ILIM: R6.2, U2.2 (ILIM), U2.9 (ILIM)
/Power/PHYPWRBJT: Q2.3 (C), R9.1
/Power/PHYPWRFET: C8.2, Q1.1 (G), R8.2, R9.2
/Power/USBCC1: J7.A5 (CC1), R2.1
/Power/USBCC2: J7.B5 (CC2), R3.1
/Power/USBCD+: D3.3 (I/O2), J7.A6 (D+), J7.B6 (D+)
/Power/USBCD-: D3.1 (I/O1), J7.A7 (D-), J7.B7 (D-)
GND: C1.2, C2.2, C3.2, C5.2, C6.2, C7.2, C11.2, C12.2, D1.1 (K), D3.2 (GND), D5.2 (A), J6.2, J7.A1 (GND), J7.A12 (GND), J7.B1 (GND), J7.B12 (GND), J7.S1 (SHIELD), Q2.2 (E), R2.2, R3.2, R5.2, R11.2, U1.2 (GND), U2.4 (GND); also elsewhere on the board
unnamed: R7.2, U2.8 (BS)

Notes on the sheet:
RESISTORS: 62,5mW WHERE NOT SPECIFIED
R_{H} = (V_{OUT} - 0,6V) * R_{L} / 0,6V V_{OUT} = (0,6 * R_{H} / R_{L}) + 0,6 V_{OUT} = (0,6 * 100k/22,1k) +0,6 V_{OUT} = 3,31V
R_{2} = R_{1}/(V_{OUT} / 0,805 - 1) V_{OUT} = (R_{1} / R_{2}) + 1) * 0,805 V_{OUT} = (300k / 52,3k + 1) * 0,805 V_{OUT} = 5,42V
24VDC
I_{LED} = (5V - V_{LED}) / 1k I_{LED} = (5V - 2.7V) / 1k I_{LED} = 2,30 mA
